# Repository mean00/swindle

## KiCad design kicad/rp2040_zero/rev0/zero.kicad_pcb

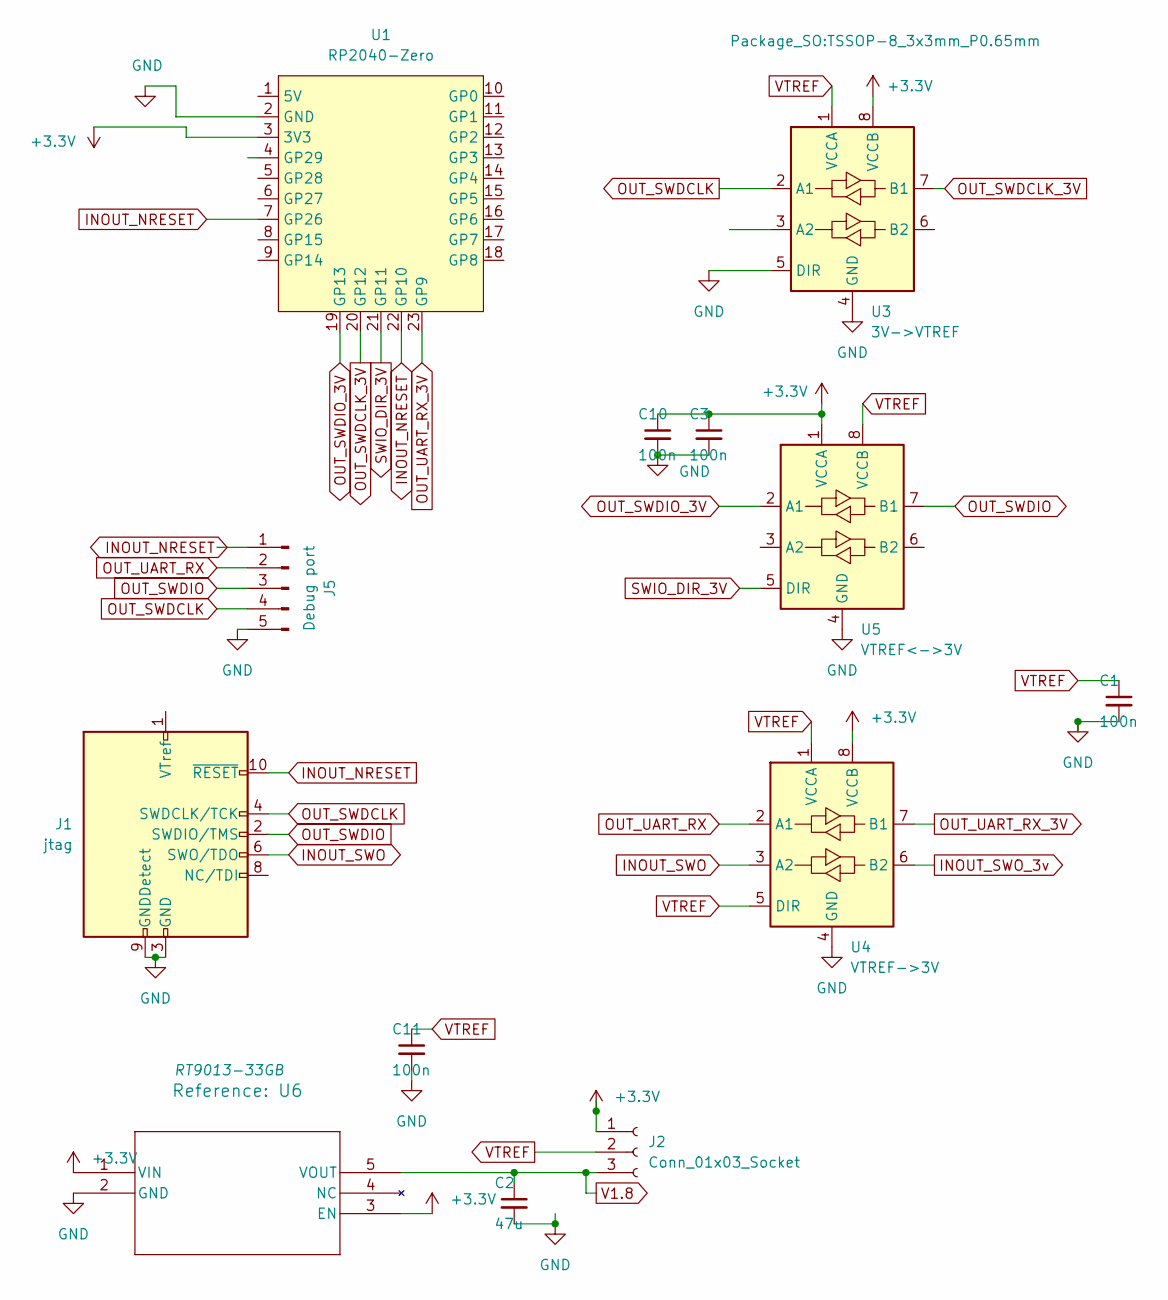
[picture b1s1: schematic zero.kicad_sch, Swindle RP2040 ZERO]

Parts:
C1, C3, C10, C11: 100n; R_0603_1608Metric
C2: 47u; R_1210_3225Metric
J1: jtag; PinHeader_2x05_P1.27mm_Vertical_SMD
J2: Conn_01x03_Socket; PinHeader_1x03_P2.54mm_Vertical
J5: Debug port; Con5
U1: RP2040-Zero; RP2040 Zero
U3: 3V->VTREF; TSSOP-8_3x3mm_P0.65mm
U4: VTREF->3V; TSSOP-8_3x3mm_P0.65mm
U5: VTREF<->3V; TSSOP-8_3x3mm_P0.65mm
U6: RT9013-33GB; TSOT-23-5

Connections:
+3.3V: C3.1, C10.1, J2.1, U1.3 (3V3), U3.8 (VCCB), U4.8 (VCCB), U5.1 (VCCA), U6.1 (VIN), U6.3 (EN)
GND: C1.2, C2.2, C3.2, C10.2, C11.2, J1.3 (GND), J1.5 (GND), J1.9 (GNDDetect), J5.5, U1.2 (GND), U3.4 (GND), U3.5 (DIR), U4.4 (GND), U5.4 (GND), U6.2 (GND)
INOUT_NRESET: J1.10 (~RESET), J5.1, U1.7 (GP26), U1.22 (GP10)
INOUT_SWO: J1.6 (SWO/TDO), U4.3 (A2)
INOUT_SWO_3v: U4.6 (B2)
OUT_SWDCLK: J1.4 (SWDCLK/TCK), J5.4, U3.2 (A1)
OUT_SWDCLK_3V: U1.20 (GP12), U3.7 (B1)
OUT_SWDIO: J1.2 (SWDIO/TMS), J5.3, U5.7 (B1)
OUT_SWDIO_3V: U1.19 (GP13), U5.2 (A1)
OUT_UART_RX: J5.2, U4.2 (A1)
OUT_UART_RX_3V: U1.23 (GP9), U4.7 (B1)
SWIO_DIR_3V: U1.21 (GP11), U5.5 (DIR)
V1.8: C2.1, J2.3, U6.5 (VOUT)
VTREF: C1.1, C11.1, J2.2, U3.1 (VCCA), U4.1 (VCCA), U4.5 (DIR), U5.8 (VCCB)

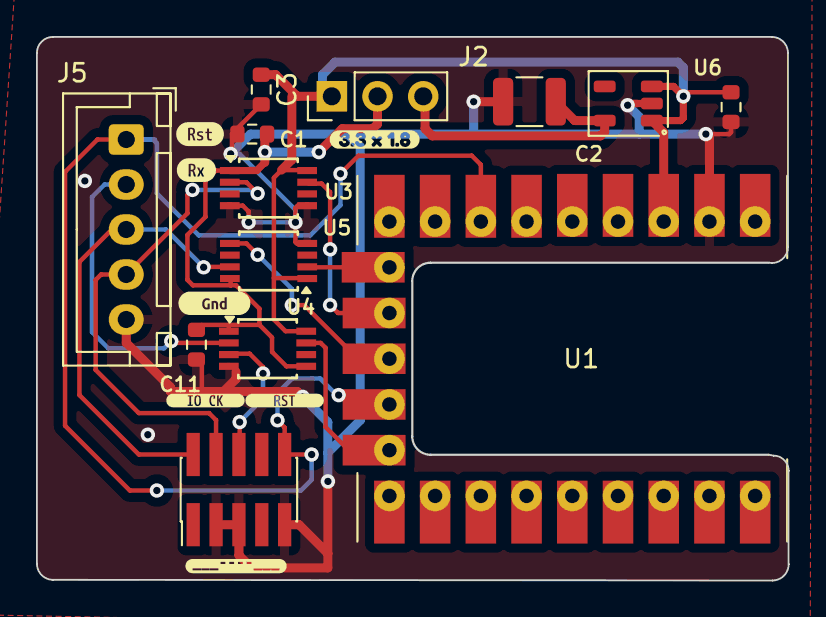
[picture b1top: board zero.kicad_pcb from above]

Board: 2 copper layers, 41.8 x 30.2 mm, 20 parts (0 on the bottom side), 13 nets.

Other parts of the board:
kibuzzard-6713DC2E: G***; kibuzzard-6713DC2E
kibuzzard-6713DC16: G***; kibuzzard-6713DC16
kibuzzard-6714FCCA: G***; kibuzzard-6714FCCA
kibuzzard-6719D5E3: G***; kibuzzard-6719D5E3
kibuzzard-6719D703: G***; kibuzzard-6719D703
kibuzzard-67310D89: G***; kibuzzard-67310D89
kibuzzard-67310DA4: G***; kibuzzard-67310DA4

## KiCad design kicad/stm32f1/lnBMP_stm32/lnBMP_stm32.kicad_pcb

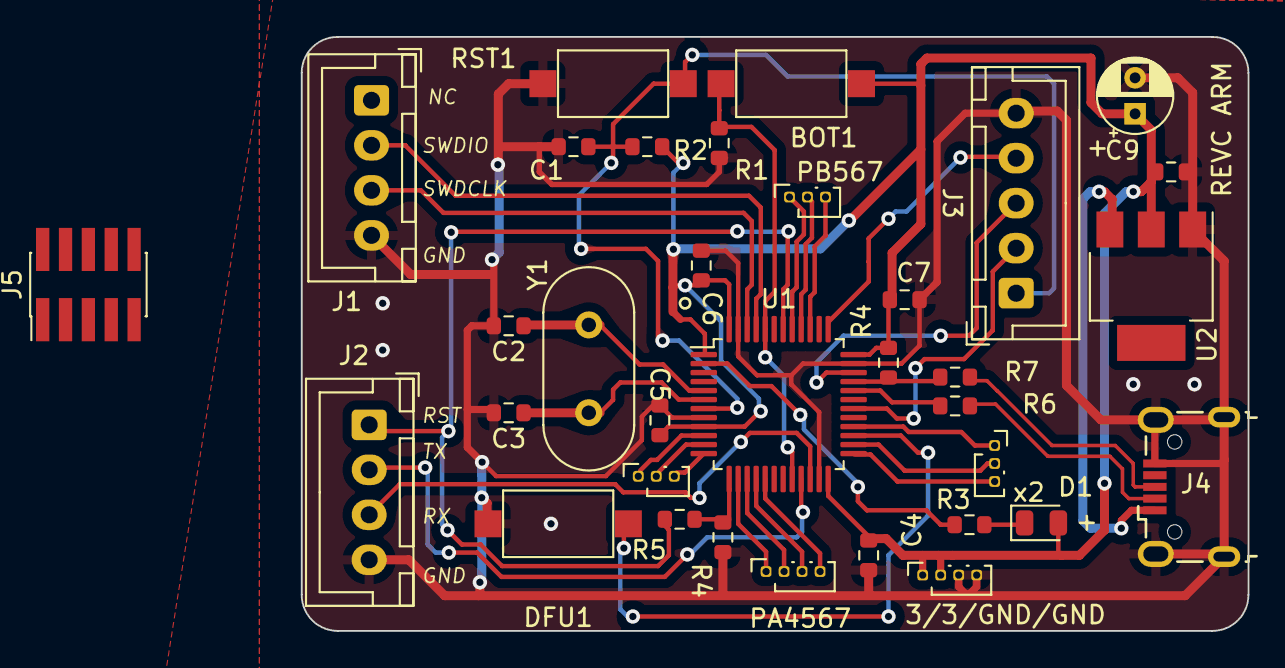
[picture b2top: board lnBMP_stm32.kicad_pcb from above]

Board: 2 copper layers, 52.6 x 33.0 mm, 33 parts (0 on the bottom side), 23 nets.

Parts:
3/3/GND/GND: PinSocket_1x04_P1.00mm_Vertical
BOT1: SW1; SW_SPST_CK_RS282G05A3
C1, C4, C5, C6, C7, C9: 100n; R_0603_1608Metric
C2, C3: 10pF; R_0603_1608Metric
C8: C_Polarized; CP_Radial_D4.0mm_P2.00mm
D1: LED; D_0805_2012Metric
DFU1: SW_DIP_x01; SW_SPST_CK_RS282G05A3
J1: BMP Debug1; JST_XH_B4B-XH-A_1x04_P2.50mm_Vertical
J2: BMP Debug2; JST_XH_B4B-XH-A_1x04_P2.50mm_Vertical
J3: Debug port; JST_XH_B5B-XH-A_1x05_P2.50mm_Vertical
J4: USB_OTG; USB_Micro-B_Wuerth_629105150521
J5: Conn_ARM_JTAG_SWD_10; PinHeader_2x05_P1.27mm_Vertical_SMD
PA4567: PinSocket_1x04_P1.00mm_Vertical
PB567: PinSocket_1x03_P1.00mm_Vertical
R1, R2: 10k; R_0603_1608Metric
R3: 330; R_0603_1608Metric
R4: R_Small; R_0603_1608Metric
R4#2: 1.2k; R_0603_1608Metric
R5: 1k; R_0603_1608Metric
R6, R7: 22; R_0603_1608Metric
RST1: SW2; SW_SPST_CK_RS282G05A3
U1: STM32F103CBTx; LQFP-48_7x7mm_P0.5mm
U2: LM1117-3.3; SOT-223
Y1: Crystal; Crystal_HC49-U_Vertical
x2: PinSocket_1x03_P1.00mm_Vertical

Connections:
+3.3V: 3/3/GND/GND.1, 3/3/GND/GND.2, BOT1.1, C4.1, C5.1, C6.1, C7.1, C8.1, C9.1, D1.2 (A), R2.1, R4#2.1, U1.1 (VBAT), U1.9 (VDDA), U1.24 (VDD), U1.36 (VDD), U1.48 (VDD), U2.2 (VO)
D+: J4.3 (D+), R7.1
D-: J4.2 (D-), R6.1
GND: 3/3/GND/GND.3, 3/3/GND/GND.4, C1.2, C2.2, C3.2, C4.2, C5.2, C6.2, C7.2, C8.2, C9.2, DFU1.2, J1.4, J2.4, J3.5, J4.5 (GND), J4.6 (Shield), J5.3 (GND), J5.5 (GND), J5.9 (GNDDetect), R1.2, R4.1, RST1.2, U1.8 (VSSA), U1.23 (VSS), U1.35 (VSS), U1.47 (VSS), U2.1 (GND)
INOUT_NRESET: J2.1, J5.10 (~RESET), R5.1, U1.42 (PB6)
IN_FORCE_DFU: DFU1.1, U1.27 (PB14)
NRST: C1.1, J3.1, R2.2, RST1.1, U1.7 (NRST)
unnamed: D1.1 (K), R3.2
unnamed: J4.1 (VBUS), U2.3 (VI)
unnamed: BOT1.2, R1.1, U1.20 (PB2), U1.44 (BOOT0)
unnamed: R4.2, R5.2, U1.13 (PA3)
unnamed: R6.2, U1.32 (PA11)
unnamed: R4#2.2, R7.2, U1.33 (PA12)
unnamed: R3.1, U1.2 (PC13)
unnamed: C2.1, U1.5 (PD0), Y1.1
unnamed: C3.1, U1.6 (PD1), Y1.2
OUT_SWDCLK: J1.3, J5.4 (SWDCLK/TCK), U1.46 (PB9)
OUT_SWDIO: J1.2, J5.2 (SWDIO/TMS), U1.45 (PB8)
OUT_UART_RX: J2.3, U1.22 (PB11)
OUT_UART_TX: J2.2, U1.21 (PB10)
SWDCLK: J3.4, U1.37 (PA14)
SWDIO: J3.3, U1.34 (PA13)
UART_TX: J3.2, U1.30 (PA9)

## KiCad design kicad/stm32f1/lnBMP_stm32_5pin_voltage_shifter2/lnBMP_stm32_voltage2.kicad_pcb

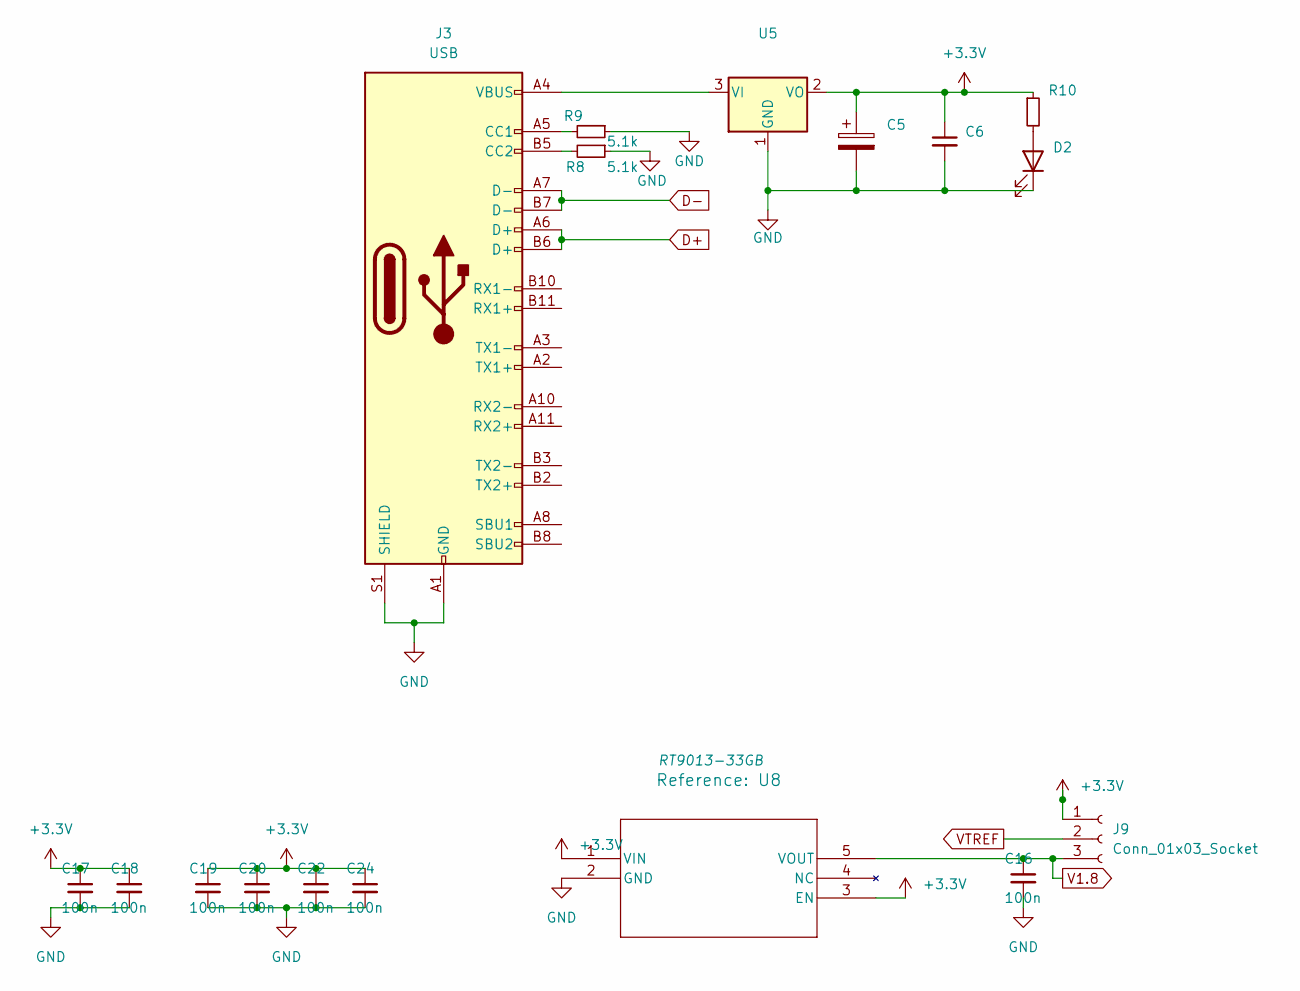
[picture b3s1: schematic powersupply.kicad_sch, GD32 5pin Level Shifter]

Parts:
C5: 100u; C_1206_3216Metric_Pad1.33x1.80mm_HandSolder
C6, C16, C17, C18, C19, C20, C22, C24: 100n; R_0603_1608Metric
D2: LED; D_0805_2012Metric
J3: USB; USB_C_Receptacle_Palconn_UTC16-G
J9: Conn_01x03_Socket; PinHeader_1x03_P1.27mm_Vertical
R8, R9: 5.1k; R_0603_1608Metric
R10: 330; R_0603_1608Metric
U5: LM1117-3.3; SOT-223
U8: RT9013-33GB; TSOT-23-5

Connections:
+3.3V: C5.1, C6.1, C17.1, C18.1, C19.1, C20.1, C22.1, C24.1, J9.1, R10.1, U5.2 (VO), U8.1 (VIN), U8.3 (EN); also elsewhere on the board
D+: J3.A6 (D+), J3.B6 (D+); also elsewhere on the board
D-: J3.A7 (D-), J3.B7 (D-); also elsewhere on the board
GND: C5.2, C6.2, C16.2, C17.2, C18.2, C19.2, C20.2, C22.2, C24.2, D2.1 (K), J3.A1 (GND), J3.A12 (GND), J3.B1 (GND), J3.B12 (GND), J3.S1 (SHIELD), R8.1, R9.1, U5.1 (GND), U8.2 (GND); also elsewhere on the board
unnamed: D2.2 (A), R10.2
unnamed: J3.A5 (CC1), R9.2
unnamed: J3.B5 (CC2), R8.2
unnamed: J3.A4 (VBUS), J3.A9 (VBUS), J3.B4 (VBUS), J3.B9 (VBUS), U5.3 (VI)
V1.8: C16.1, J9.3, U8.5 (VOUT)
VTREF: J9.2; also elsewhere on the board

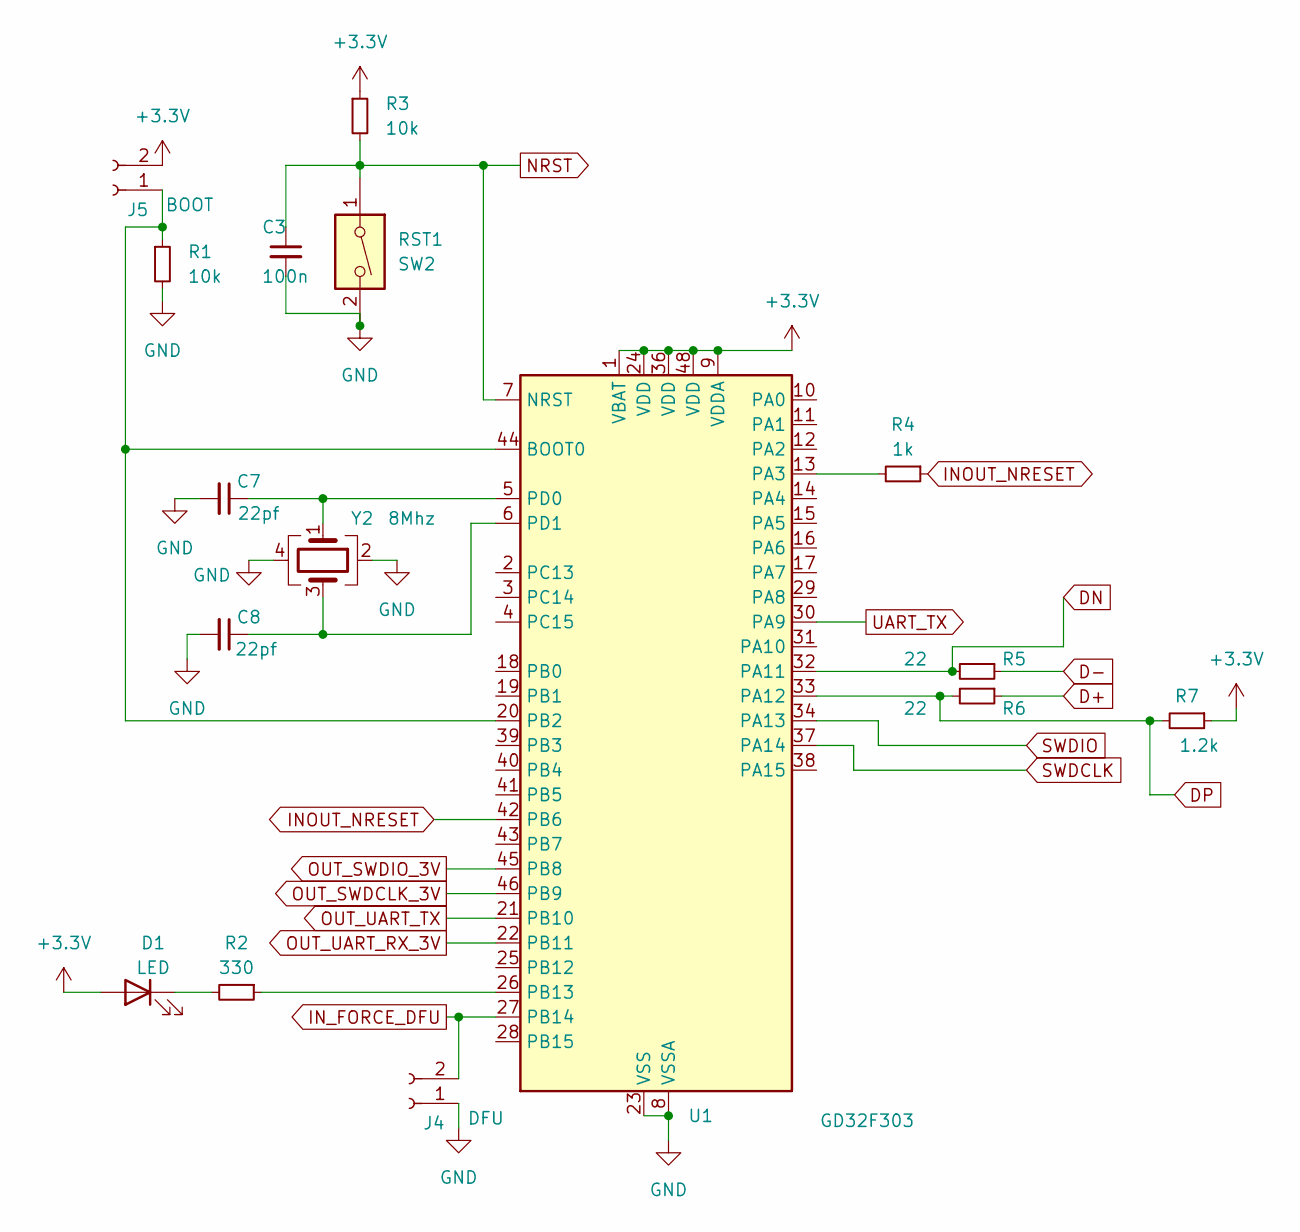
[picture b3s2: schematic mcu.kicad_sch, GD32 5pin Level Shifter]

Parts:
C3: 100n; R_0603_1608Metric
C7, C8: 22pf; R_0603_1608Metric
D1: LED; D_0805_2012Metric
J4: DFU; PinHeader_1x02_P1.27mm_Vertical
J5: BOOT; PinHeader_1x02_P1.27mm_Vertical
R1, R3: 10k; R_0603_1608Metric
R2: 330; R_0603_1608Metric
R4: 1k; R_0603_1608Metric
R5, R6: 22; R_0603_1608Metric
R7: 1.2k; R_0603_1608Metric
RST1: SW2; SW_SPST_CK_RS282G05A3
U1: GD32F303; LQFP-48_7x7mm_P0.5mm
Y2: 8Mhz; Crystal_SMD_TXC_7M-4Pin_3.2x2.5mm

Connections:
+3.3V: D1.2 (A), J5.2, R3.1, R7.1, U1.1 (VBAT), U1.9 (VDDA), U1.24 (VDD), U1.36 (VDD), U1.48 (VDD); also elsewhere on the board
D+: R6.1; also elsewhere on the board
D-: R5.1; also elsewhere on the board
DN: R5.2, U1.32 (PA11)
DP: R6.2, R7.2, U1.33 (PA12)
GND: C3.2, C7.2, C8.2, J4.1, R1.2, RST1.2, U1.8 (VSSA), U1.23 (VSS), U1.35 (VSS), U1.47 (VSS), Y2.2, Y2.4; also elsewhere on the board
INOUT_NRESET: R4.1, U1.42 (PB6); also elsewhere on the board
IN_FORCE_DFU: J4.2, U1.27 (PB14)
NRST: C3.1, R3.2, RST1.1, U1.7 (NRST); also elsewhere on the board
unnamed: D1.1 (K), R2.2
unnamed: J5.1, R1.1, U1.20 (PB2), U1.44 (BOOT0)
unnamed: R4.2, U1.13 (PA3)
unnamed: R2.1, U1.26 (PB13)
unnamed: C7.1, U1.5 (PD0), Y2.1
unnamed: C8.1, U1.6 (PD1), Y2.3
OUT_SWDCLK_3V: U1.46 (PB9); also elsewhere on the board
OUT_SWDIO_3V: U1.45 (PB8); also elsewhere on the board
OUT_UART_RX_3V: U1.22 (PB11); also elsewhere on the board
OUT_UART_TX: U1.21 (PB10)
SWDCLK: U1.37 (PA14); also elsewhere on the board
SWDIO: U1.34 (PA13); also elsewhere on the board
UART_TX: U1.30 (PA9); also elsewhere on the board

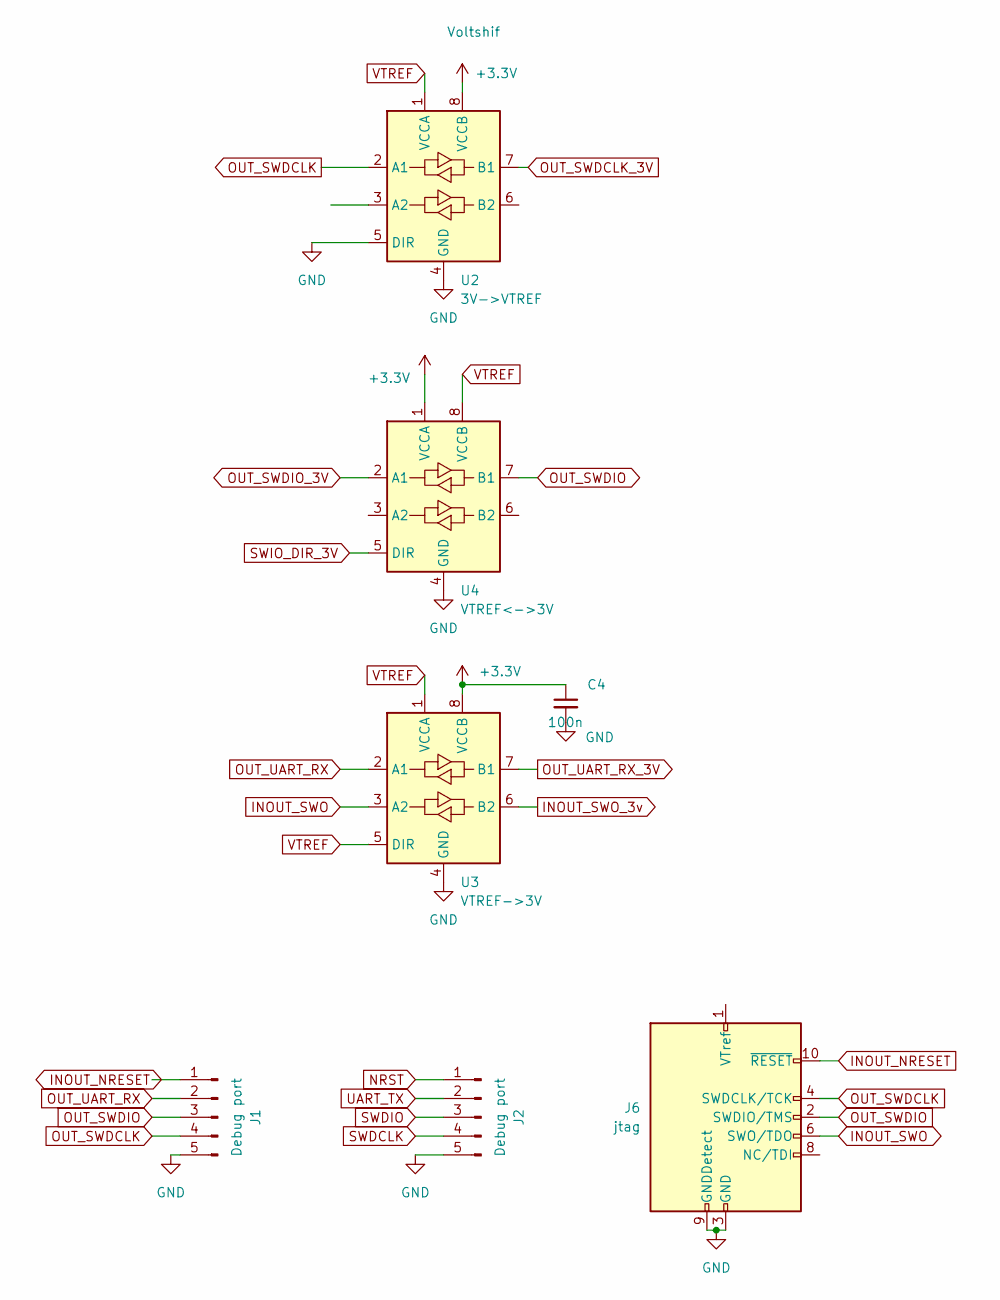
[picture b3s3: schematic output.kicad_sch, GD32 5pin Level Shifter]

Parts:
C4: 100n; R_0603_1608Metric
J1, J2: Debug port; JST_XH_B5B-XH-AM_1x05_P2.50mm_Vertical
J6: jtag; PinHeader_2x05_P1.27mm_Vertical_SMD
U2: 3V->VTREF; Voltshif
U3: VTREF->3V; VSSOP-8_2.3x2mm_P0.5mm
U4: VTREF<->3V; VSSOP-8_2.3x2mm_P0.5mm

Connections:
+3.3V: C4.1, U2.8 (VCCB), U3.8 (VCCB), U4.1 (VCCA); also elsewhere on the board
GND: C4.2, J1.5, J2.5, J6.3 (GND), J6.5 (GND), J6.9 (GNDDetect), U2.4 (GND), U2.5 (DIR), U3.4 (GND), U4.4 (GND); also elsewhere on the board
INOUT_NRESET: J1.1, J6.10 (~RESET); also elsewhere on the board
INOUT_SWO: J6.6 (SWO/TDO), U3.3 (A2)
INOUT_SWO_3v: U3.6 (B2)
NRST: J2.1; also elsewhere on the board
OUT_SWDCLK: J1.4, J6.4 (SWDCLK/TCK), U2.2 (A1)
OUT_SWDCLK_3V: U2.7 (B1); also elsewhere on the board
OUT_SWDIO: J1.3, J6.2 (SWDIO/TMS), U4.7 (B1)
OUT_SWDIO_3V: U4.2 (A1); also elsewhere on the board
OUT_UART_RX: J1.2, U3.2 (A1)
OUT_UART_RX_3V: U3.7 (B1); also elsewhere on the board
SWDCLK: J2.4; also elsewhere on the board
SWDIO: J2.3; also elsewhere on the board
SWIO_DIR_3V: U4.5 (DIR)
UART_TX: J2.2; also elsewhere on the board
VTREF: U2.1 (VCCA), U3.1 (VCCA), U3.5 (DIR), U4.8 (VCCB); also elsewhere on the board

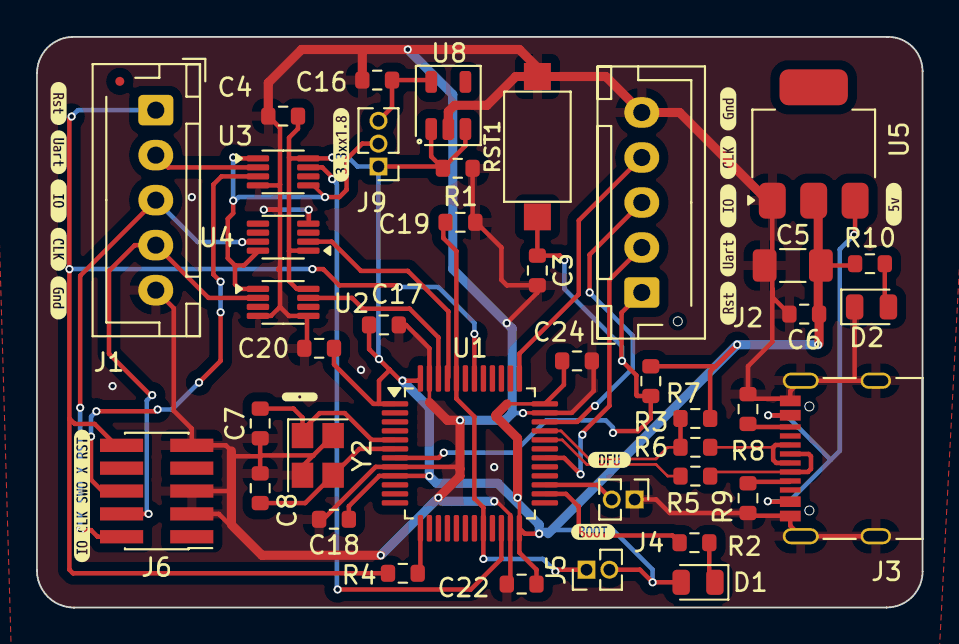
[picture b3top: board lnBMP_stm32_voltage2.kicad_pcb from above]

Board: 2 copper layers, 49.2 x 31.7 mm, 56 parts (0 on the bottom side), 31 nets.

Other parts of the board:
kibuzzard-672226BD: G***; kibuzzard-672226BD
kibuzzard-672281C9, kibuzzard-672281C9#2: G***; kibuzzard-672281C9
kibuzzard-672281D4, kibuzzard-672281D4#2: G***; kibuzzard-672281D4
kibuzzard-672281DC, kibuzzard-672281DC#2: G***; kibuzzard-672281DC
kibuzzard-672281E9, kibuzzard-672281E9#2: G***; kibuzzard-672281E9
kibuzzard-672282C7: G***; kibuzzard-672282C7
kibuzzard-672283BF: G***; kibuzzard-672283BF
kibuzzard-6722820B, kibuzzard-6722820B#2: G***; kibuzzard-6722820B
kibuzzard-6722831C: G***; kibuzzard-6722831C
kibuzzard-67228234: G***; kibuzzard-67228234
kibuzzard-67228302: G***; kibuzzard-67228302
